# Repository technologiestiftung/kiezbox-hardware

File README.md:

# kiezbox-pcb
This folder contains the wiring diagrams for the hardware components. The folders can be opened with KiCad. One is for the sensor module and one is for the Kiezbox core. There is also a PFD showing the layout of the hardware in the control cabinet. It also shows where to drill the holes for the solar cable and the hole for the outdoor temperature sensor.

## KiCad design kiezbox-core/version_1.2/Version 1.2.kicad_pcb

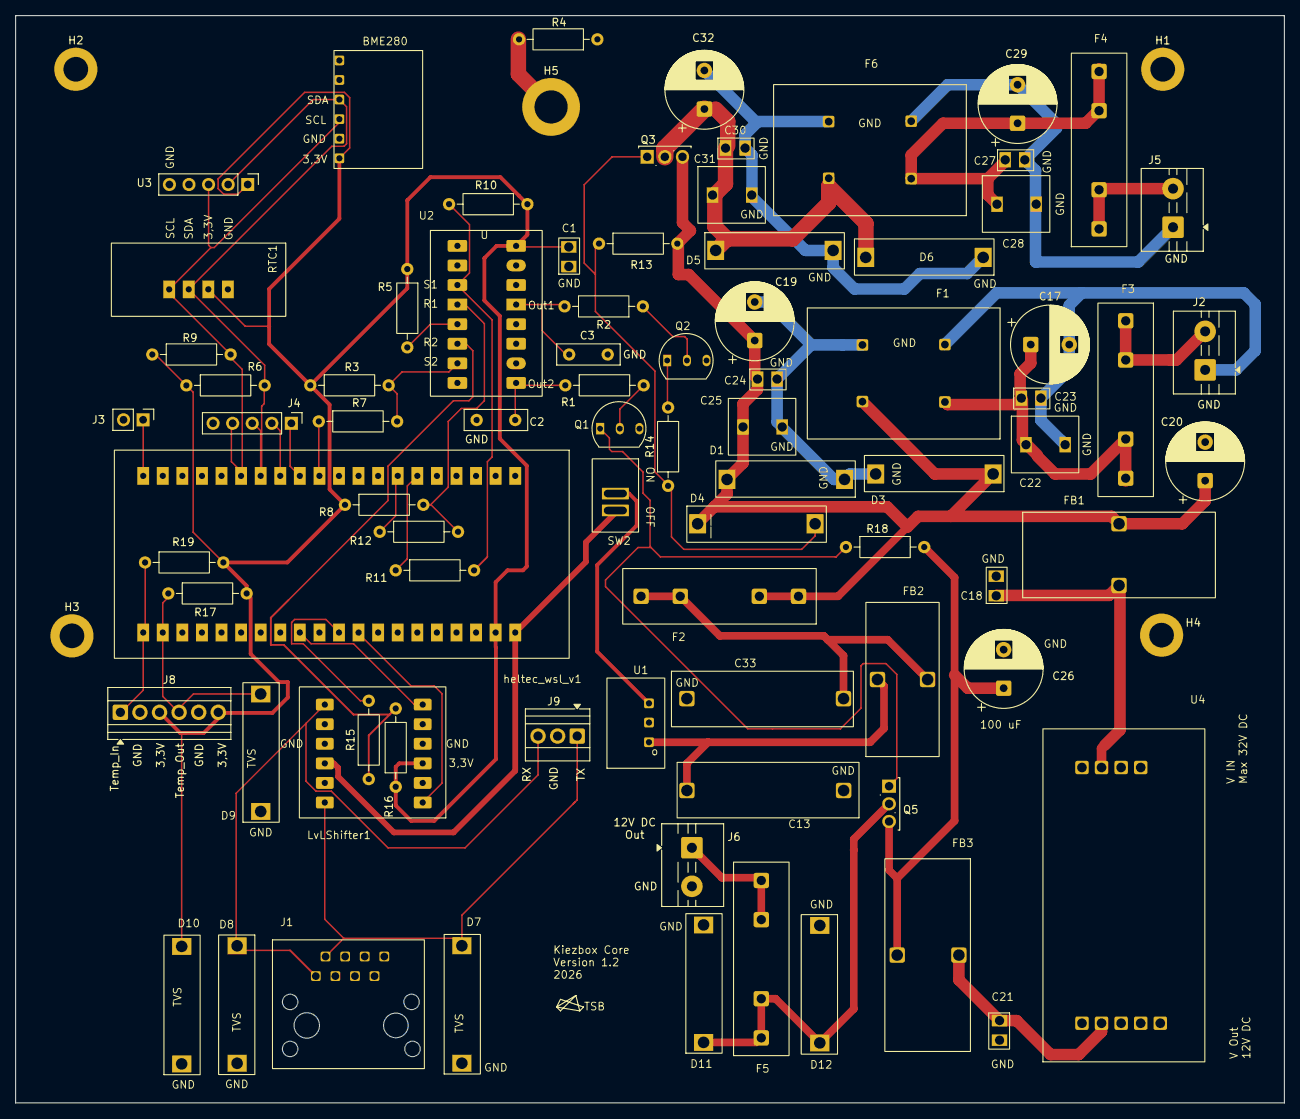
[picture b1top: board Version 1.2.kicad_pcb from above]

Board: 2 copper layers, 164.6 x 141.1 mm, 86 parts (0 on the bottom side), 45 nets.

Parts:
BME280: BME280
C1, C18, C21, C23, C24, C27, C30: 100 nF; 100nF
C2, C3: 47 pF; C_Disc_D8.0mm_W2.5mm_P5.00mm
C13, C33: 4,7 uF
C17, C19, C20, C26, C29, C32: 100 uF; CP_Radial_D10.0mm_P5.00mm
C22, C25, C28, C31: 1uF
D1, D6: D_TVS_36; TVS_groß
D3, D5: D_Schottky 40V 5A; TVS_groß
D4: BZX 85C15 VIS; TVS_groß
D7, D8, D9, D10: TVS; TVS_groß
D11: D_Schottky 20V 3A; TVS_groß
D12: TVS 20,5V; TVS_groß
F1, F6: Netzdrossel, 1mH, 6A; Filter_Leistung
F2: 1,6 A; Sicherunghalter
F3: Schnell Fuse 5A; Sicherunghalter
F4: 3,15 A träge; Sicherunghalter
F5: Schnell Fuse 2A_Starlink_15A; Sicherunghalter
FB1, FB3: Funk-Entstördrossel, 6 A, 100 µH; Filter polo
FB2: Ringkerndrosseln TLC 2,5A - 10 µH; Filter TSR
H1, H2, H3, H4: MountingHole; MountingHole_3.2mm_M3_DIN965_Pad
H5: MountingHole_Pad; MountingHole_4.3mm_M4_DIN965_Pad
J1: RJ45
J2: Input AKKU/Netzgerät; TerminalBlock_MaiXu_MX126-5.0-02P_1x02_P5.00mm
J3: JTAG Modus Auswahl; PinHeader_1x02_P2.54mm_Vertical
J4: JTAG-Schnittstelle; PinHeader_1x05_P2.54mm_Vertical
J5: Output Starlink Mini; TerminalBlock_MaiXu_MX126-5.0-02P_1x02_P5.00mm
J6: 12 Out für Banana Pi; TerminalBlock_MaiXu_MX126-5.0-02P_1x02_P5.00mm
J8: (alt)Sensoranschlusse TemIn/Out; TerminalBlock_Xinya_XY308-2.54-6P_1x06_P2.54mm_Horizontal
J9: Victron RX/TX; TerminalBlock_Xinya_XY308-2.54-3P_1x03_P2.54mm_Horizontal
LvLShifter1: lvlshifter
Q1, Q2: BC546; Transistor
Q3, Q5: IRFU9024; TO-251-3_Vertical
R1, R2, R5, R6, R9: 10 K; R_Axial_DIN0207_L6.3mm_D2.5mm_P10.16mm_Horizontal
R3, R16: 10K; R_Axial_DIN0207_L6.3mm_D2.5mm_P10.16mm_Horizontal
R4: 0; R_Axial_DIN0207_L6.3mm_D2.5mm_P10.16mm_Horizontal
R7, R11, R12, R15: 3,6 K; R_Axial_DIN0207_L6.3mm_D2.5mm_P10.16mm_Horizontal
R8, R10: 10k; R_Axial_DIN0207_L6.3mm_D2.5mm_P10.16mm_Horizontal
R13, R18: 100 K; R_Axial_DIN0207_L6.3mm_D2.5mm_P10.16mm_Horizontal
R14: 47k; R_Axial_DIN0207_L6.3mm_D2.5mm_P10.16mm_Horizontal
R17, R19: 4,7 K; R_Axial_DIN0207_L6.3mm_D2.5mm_P10.16mm_Horizontal
RTC1: RTC
SW2: SW_DPST_x2; Unbenannt
U1: DC/DC-Wandler TSR-1, 1 W, 5 V, 1000 mA, SIL / TO-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; TSR1-2450
U2: CMOS-Vierfach-NAND-R/S-Latch, 3 - 18 V, 6,8mA, DI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; Latch 16 Pin
U3: DS3231 Real Time Clock Modul für Raspberry Pi; PinHeader_1x05_P2.54mm_Vertical
U4: Pololu 12V Step-Up Step-Down Spannungsregler S18V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; Pololu12
heltec_wsl_v1: Heltec_v3_lite

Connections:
GND: BME280.GND, C1.1, C2.2, C3.2, C13.1, C17.2, C18.2, C19.2, C20.2, C21.2, C22.2, C23.2, C24.2, C25.2, C26.2, C27.2, C28.2, C29.2, C30.2, C31.2, C32.2, C33.1, D1.1 (A1), D3.2 (A), D5.2 (A), D6.1 (A1), D7.1 (A1), D8.2 (A2), D9.1 (A1), D10.1 (A1), D11.2 (A), D12.1 (A1), F1.2, F1.3, F6.2, F6.3, J1.6, J2.1, J3.2, J4.5, J5.1, J6.2, J8.2 (GND), J8.5 (GND), J9.2 (GND), LvLShifter1.4 (GND), LvLShifter1.10 (GND), Q1.3 (E), Q2.3 (E), R4.1, RTC1.1 (GND), U1.2 (GND), U2.8 (VSS), U2.11 (S3), U2.12 (R3), U2.14 (R4), U2.15 (S4), U3.5 (GND), U4.4 (GND), U4.9 (GND), heltec_wsl_v1.2 (GND), heltec_wsl_v1.23 (GND)
unnamed: BME280.VCC (3,3V_Input), C1.2, D10.2 (A2), J8.3 (3,3V), J8.6 (3,3V), LvLShifter1.3 (3,3V), R3.1, R5.1, R6.1, R8.1, R9.1, R10.1, R16.1, R17.2, R19.2, RTC1.2 (VCC), U2.16 (VDD), U3.1 (3,3V), heltec_wsl_v1.22 (3V3_IN)
unnamed: C17.1, C22.1, C23.1, F1.1, F3.2
unnamed: C27.1, C28.1, C29.1, F4.2, F6.1
unnamed: C33.2, F2.2, FB2.2
unnamed: C19.1, C20.1, C24.1, C25.1, D1.2 (A2), D3.1 (K), D4.1 (K), F1.4, F2.1, FB1.1, Q3.3 (S), R13.2
unnamed: D4.2 (A), Q3.1 (G), R13.1, R14.1
unnamed: C30.1, C31.1, C32.1, D5.1 (K), D6.2 (A2), F6.4, Q3.2 (D)
unnamed: D7.2 (A2), J1.7, J9.1 (TX), LvLShifter1.7 (TX0_5V_In)
unnamed: D8.1 (A1), J1.8, J9.3 (RX), LvLShifter1.12 (TX1)
unnamed: D9.2 (A2), J8.4 (Temp_Out), R17.1, heltec_wsl_v1.39 (GPIO5/Temp_Out)
unnamed: D11.1 (K), D12.2 (A2), F5.1, Q5.2 (D)
unnamed: H5.1 (1_1), R4.2
unnamed: F3.1, J2.2
unnamed: J3.1, heltec_wsl_v1.20 (GIPO03)
unnamed: J4.1, heltec_wsl_v1.12 (GIPO39)
unnamed: J4.2, heltec_wsl_v1.13 (GIPO40)
unnamed: BME280.SDA, J4.3, R6.2, RTC1.3 (SDA), U3.2 (SDA), heltec_wsl_v1.14 (GIPO41/SDA)
unnamed: BME280.SCL, J4.4, R9.2, RTC1.4 (SCL), U3.3 (SCL/SCK), heltec_wsl_v1.15 (GIPO42/SCL)
unnamed: F4.1, J5.2
unnamed: F5.2, J6.1
unnamed: LvLShifter1.9 (5V), SW2.2 (B), heltec_wsl_v1.21 (5V_IN)
unnamed: LvLShifter1.6 (TX1_3V_In), heltec_wsl_v1.32 (GIPO17/V_TX)
unnamed: Q1.2 (B), R1.2
unnamed: Q1.1 (C), Q5.1 (G), R18.1
unnamed: Q2.2 (B), R2.1
unnamed: Q2.1 (C), R14.2
unnamed: C26.1, FB3.2, Q5.3 (S), R18.2
unnamed: SW2.1 (A), U1.3 (Vout)
unnamed: C13.2, FB2.1, U1.1 (Vin)
unnamed: R5.2, U2.5 (ENABLE)
unnamed: C3.1, R2.2, U2.13 (Q1)
unnamed: C2.1, R1.1, U2.9 (Q2)
unnamed: R8.2, R12.2, U2.4 (R1)
unnamed: R15.1, R16.2, U2.6 (R2)
unnamed: R10.2, R11.2, U2.3 (S1)
unnamed: R3.2, R7.2, U2.7 (S2)
unnamed: C18.1, FB1.2, U4.7 (VIN)
unnamed: C21.1, FB3.1, U4.2 (VOUT)
unnamed: LvLShifter1.1 (TX1), heltec_wsl_v1.29 (GIPO18/V_RX)
unnamed: R15.2, heltec_wsl_v1.30 (GIPO21/Reset_2)
unnamed: R11.1, heltec_wsl_v1.6 (GIPO33/Set)
unnamed: R12.1, heltec_wsl_v1.7 (GIPO34/Reset)
unnamed: R7.1, heltec_wsl_v1.11 (GIPO38/Set_2)
unnamed: J8.1 (3,3V), R19.1, heltec_wsl_v1.40 (GPIO4/Temp_In)

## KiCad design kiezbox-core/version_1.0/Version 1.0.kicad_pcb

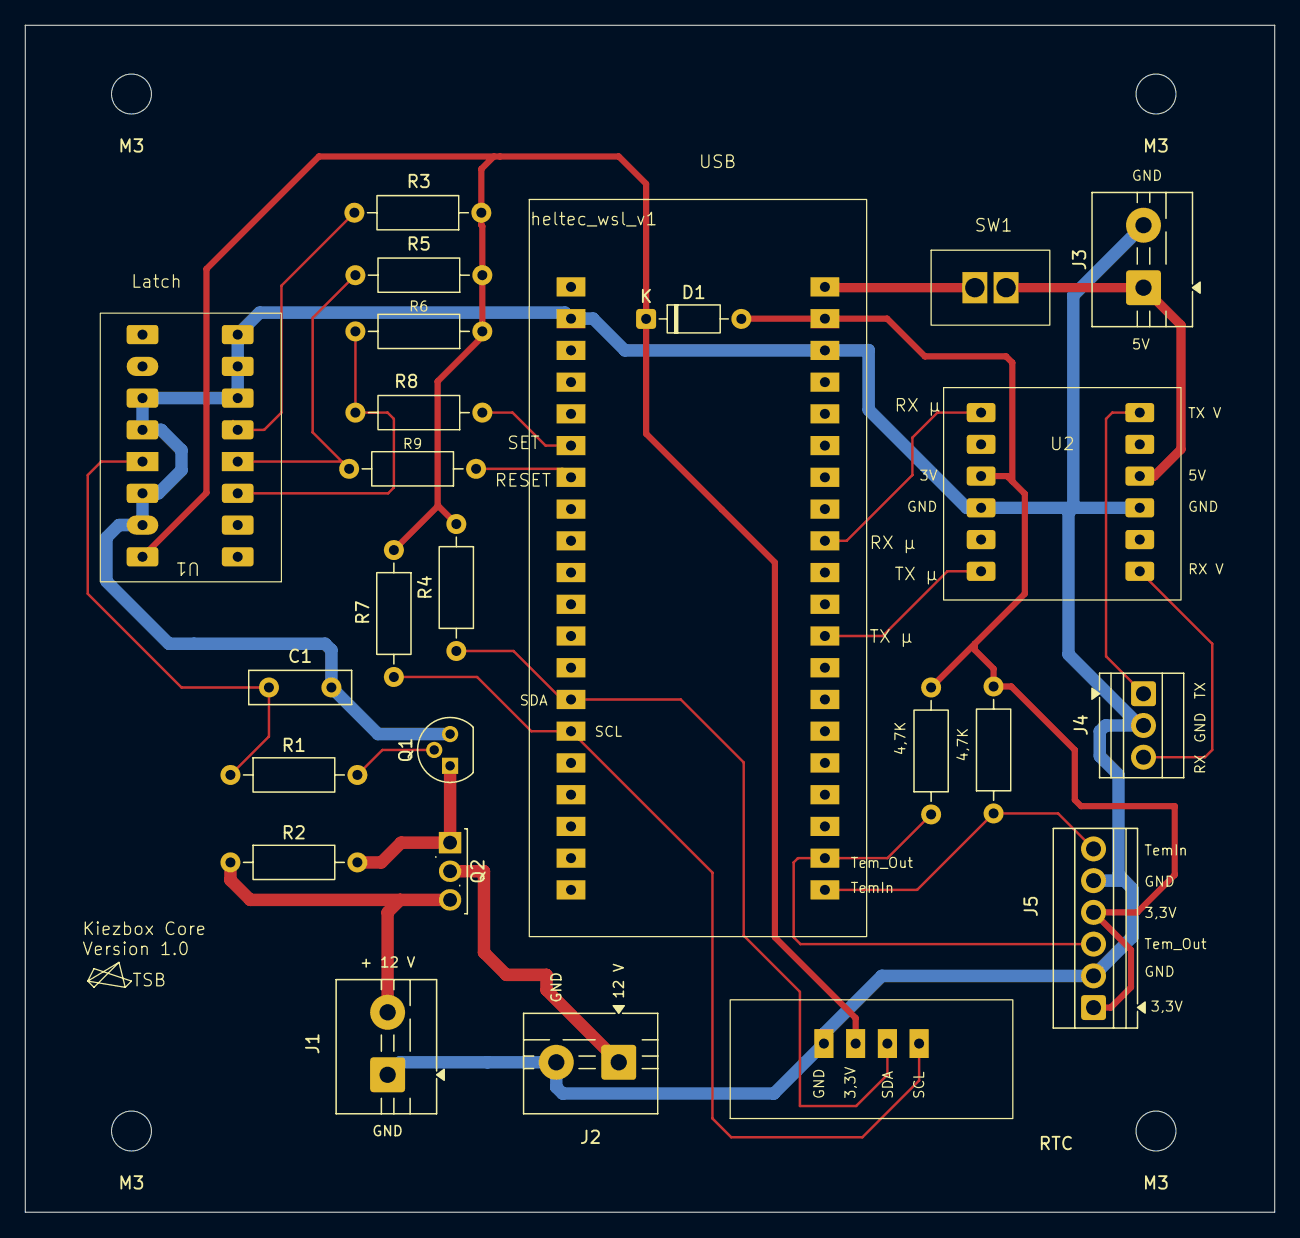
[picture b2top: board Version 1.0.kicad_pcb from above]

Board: 2 copper layers, 100.0 x 95.0 mm, 29 parts (0 on the bottom side), 23 nets.

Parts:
C1: 47 pF; C_Disc_D8.0mm_W2.5mm_P5.00mm
D1: 1N4148; D_DO-35_SOD27_P7.62mm_Horizontal
J1: 12 V In; TerminalBlock_MaiXu_MX126-5.0-02P_1x02_P5.00mm
J2: 12 Out; TerminalBlock_MaiXu_MX126-5.0-02P_1x02_P5.00mm
J3: 5V; TerminalBlock_MaiXu_MX126-5.0-02P_1x02_P5.00mm
J4: Victron; TerminalBlock_Xinya_XY308-2.54-3P_1x03_P2.54mm_Horizontal
J5: Sensoren_TemOut_TemIn; TerminalBlock_Xinya_XY308-2.54-6P_1x06_P2.54mm_Horizontal
M3, M3#2, M3#3, M3#4: MountingHole_3.2mm_M3
Q1: BC546; TO-92
Q2: IRFU9024; TO-251-3_Vertical
R1, R3, R4, R7: 10 K; R_Axial_DIN0207_L6.3mm_D2.5mm_P10.16mm_Horizontal
R2: 100 K; R_Axial_DIN0207_L6.3mm_D2.5mm_P10.16mm_Horizontal
R5, R6: 10k; R_Axial_DIN0207_L6.3mm_D2.5mm_P10.16mm_Horizontal
R8, R9: 3,6 K; R_Axial_DIN0207_L6.3mm_D2.5mm_P10.16mm_Horizontal
R10, R11: 4,7 K; R_Axial_DIN0207_L6.3mm_D2.5mm_P10.16mm_Horizontal
RTC1: RTC
SW1: SW_DPST_x2; Unbenannt
U1: Latch 16 Pin
U2: lvlshifter
heltec_wsl_v1: Heltec_v3_lite

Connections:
GND: C1.2, J1.1, J2.2, J3.2, J4.2 (GND), J5.2 (GND), J5.5 (GND), Q1.3 (E), RTC1.1 (GND), U1.6 (R2), U1.7 (S2), U1.8 (VSS), U1.11 (S3), U1.12 (R3), U1.14 (R4), U1.15 (S4), U2.4 (GND), U2.10 (GND), heltec_wsl_v1.2 (GND), heltec_wsl_v1.23 (GND)
unnamed: D1.2 (A), J5.1 (3,3V_Input), J5.4 (3,3V), R10.2, R11.2, U2.3 (3,3V), heltec_wsl_v1.22 (3V3_Out)
unnamed: D1.1 (K), R3.1, R4.1, R5.1, R6.1, R7.1, RTC1.2 (VCC), U1.16 (VDD)
unnamed: J1.2, Q2.3 (S), R2.1
unnamed: J2.1, Q2.2 (D)
unnamed: J3.1, SW1.2 (B), U2.9 (5V)
unnamed: J4.3 (RX), U2.12 (TX1)
unnamed: J4.1 (TX), U2.7 (TX0_5V_In)
unnamed: J5.6 (Temp_IN), R10.1, heltec_wsl_v1.40 (GPIO4/Temp_In)
unnamed: J5.3 (Temp_OUT), R11.1, heltec_wsl_v1.39 (GPIO5/Temp_Out)
unnamed: Q1.2 (B), R1.2
unnamed: Q1.1 (C), Q2.1 (G), R2.2
unnamed: R7.2, RTC1.4 (SCL), heltec_wsl_v1.15 (GIPO42/SCL)
unnamed: R4.2, RTC1.3 (SDA), heltec_wsl_v1.14 (GIPO41/SDA)
unnamed: SW1.1 (A), heltec_wsl_v1.21 (5V_IN)
unnamed: R3.2, U1.5 (ENABLE)
unnamed: C1.1, R1.1, U1.13 (Q1)
unnamed: R5.2, R9.2, U1.4 (R1)
unnamed: R6.2, R8.2, U1.3 (S1)
unnamed: U2.6 (TX1_3V_In), heltec_wsl_v1.32 (GIPO17/V_TX)
unnamed: U2.1 (TX1), heltec_wsl_v1.29 (GIPO18/V_RX)
unnamed: R8.1, heltec_wsl_v1.6 (GIPO33/SET)
unnamed: R9.1, heltec_wsl_v1.7 (GIPO34/Reset)

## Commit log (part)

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2025-11-21 Revise README for hardware component details
    Updated README to provide detailed information about wiring diagrams and hardware layout.
